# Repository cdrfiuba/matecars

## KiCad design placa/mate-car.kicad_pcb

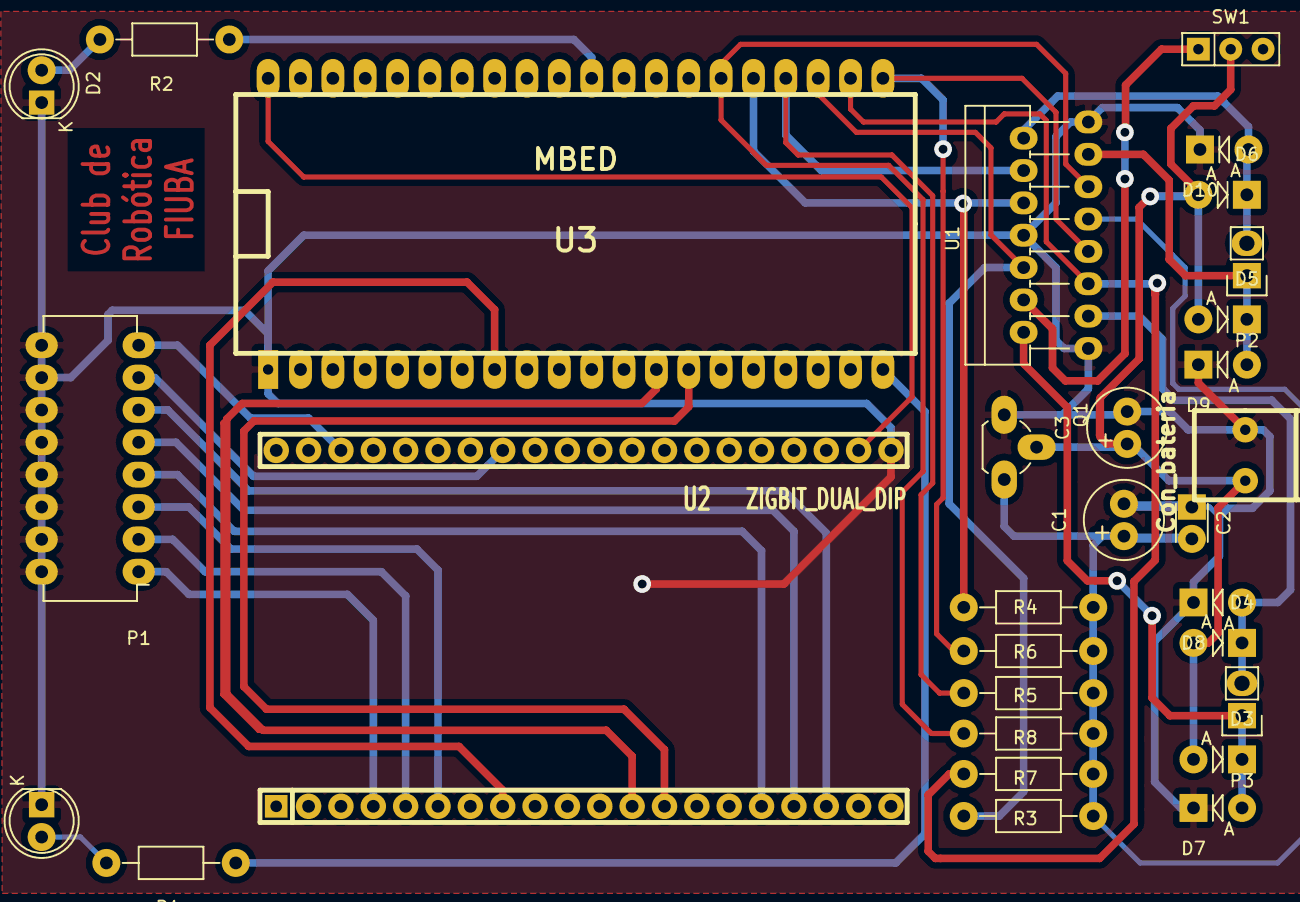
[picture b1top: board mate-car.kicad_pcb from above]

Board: 2 copper layers, 30 parts (0 on the bottom side), 30 nets.

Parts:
C1: 100u; Elko_vert_11.2x6.3mm_RM2.5
C2: 100n; C_Disc_D3_P2.5
C3: CP; Elko_vert_11.2x6.3mm_RM2.5
D1, D2: LED; LED-5MM
D3, D4, D5, D6, D7, D8, D9, D10: DIODE; Diode_DO-41_SOD81_Vertical_AnodeUp
P1: DIL16; DIP-16_W7.62mm
P2: Motor_1; Pin_Header_Straight_1x02
P3: Motor_2; Pin_Header_Straight_1x02
P4: Con_bateria; molex_2_recto
Q1: HT7550; TO-92_Rugged
R1, R2: 120; Resistor_Horizontal_RM10mm
R3, R4, R5, R6, R7, R8: 10k; Resistor_Horizontal_RM10mm
SW1: SWITCH; SW_Micro_SPST
U1: L298(H)N; Multiwatt_15_Vertical
U2: ZIGBIT_DUAL_DIP; ZIGBIT_DIP_40
U3: MBED

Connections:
/5V: C1.1, C2.2, Q1.3, R3.1, R4.1, R5.1, R6.1, R7.1, R8.1, U1.9
/DIPSW_1: P1.1, U2.4
/DIPSW_2: P1.2, U2.5
/DIPSW_3: P1.3, U2.6
/DIPSW_4: P1.4, U2.16
/DIPSW_5: P1.5, U2.17
/DIPSW_6: P1.6, U2.18
/DIPSW_7: P1.7, U2.33
/DIPSW_8: P1.8, U2.38
/L298N_5: R3.2, U1.5, U3.22
/L298N_6: R4.2, U1.6, U3.23
/L298N_7: R5.2, U1.7, U3.21
/L298N_10: R6.2, U1.10, U3.25
/L298N_11: R7.2, U1.11, U3.26
/L298N_12: R8.2, U1.12, U3.24
/LED_DERECHO: R2.1, U3.30
/LED_IZQUIERDO: R1.1, U3.20
/Motor1_A: D5.1, D9.2, P2.1, U1.13
/Motor1_B: D6.1, D10.2, P2.2, U1.14
/Motor2_A: D3.1, D7.2, P3.1, U1.2
/Motor2_B: D4.1, D8.2, P3.2, U1.3
/VCC3_3V: U2.22, U3.40
/Vcc: C3.1, D3.2, D4.2, D5.2, D6.2, P4.1, Q1.2, SW1.2
/Vs: SW1.1, U1.4
/ZB_RESET: U2.8, U3.8
/ZIGBIT_RX: U2.12, U3.13
/ZIGBIT_TX: U2.13, U3.14
GND: C1.2, C2.1, C3.2, D1.1, D2.1, D7.1, D8.1, D9.1, D10.1, P1.9, P1.10, P1.11, P1.12, P1.13, P1.14, P1.15, P1.16, P4.2, Q1.1, U1.1, U1.8, U1.15, U2.21, U3.1
unnamed: D1.2, R1.2
unnamed: D2.2, R2.2

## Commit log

2016-03-05 Subo el repo que estaba en el chilli
